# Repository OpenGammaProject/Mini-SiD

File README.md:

# Mini SiPM Driver (SiD) Board

**This is the latest hardware revision 4.x. For older revisions, please have a look at the [other branches](https://github.com/OpenGammaProject/Mini-SiD/branches). A comparison between the revision 3 and 4 hardware can be found [here on Hackaday](https://hackaday.io/project/188090-mini-sipm-driver-board/log/225429-revision-4-is-finally-here).**

**This project is on [Hackaday.io](https://hackaday.io/project/188090-mini-sipm-driver-board), where I also post project logs, progress updates and other announcements.**

Minimalistic board that allows you to quickly and easily utilize a silicon photomultiplier (SiPM) within your other projects. Supports a range of input voltages, has a digital (TTL) pulse output for the registered counts and a direct output for the SiPM pulses for easy expansion. Similar to the original [Open Gamma Detector](https://github.com/OpenGammaProject/Open-Gamma-Detector), but without any direct way to perform gamma spectroscopy.

All you need to build your own scintillation counter is this board, a scintillator and SiPM. The benefits of such a scintillation counter are that you can use it just like a Geiger counter, but it's much more sensitive, can be smaller, doesn't need 300+ Volts and you can also use it to do spectroscopy with some additional components. It mostly only registers gamma radiation though, so keep that in mind!

## How To Get One

* You can check out the project on PCBWay (affiliate) and if you buy through their service, it supports the project a little, and doesn’t cost you anything extra.
* Otherwise, use a PCB manufacturer and an electronics distributor of your choice and proceed on your own. All the files you'll need can be found in this repo.
* If you don't want to deal with all of that, feel free to contact me. Just send me an e-mail and I can help you out with the process.

**You will also need to buy a SiPM (e.g. the MICROFC-60035-SMT-TR) and scintillator (NaI(Tl) recommended) separately at a distributor of your choice.**

## Specifications

Here are some of the most important key facts:

* Compact design: Total size 100 x 25 mm. 50 x 25 mm area for electronics and additional 50 x 25 mm to mount a small scintillator.
* Input voltage: 3.1 V - 5.5 V.
* Low-voltage device: No HV needed like with a photomultiplier tube.
* SiPM voltage range from 27.5 V to 33.8 V.
* Low power consumption: <4 mA @ 5 V in standard operation.
* Adjustable gain for the SiPM pulses, also affects pulse decay time and therefore dead time.
* TTL output for counting pulses or time-over-threshold applications.
* Additional raw pulse output if you want to manipulate the signal or use it for spectroscopy.
* Dead time only limited by the speed of the scintillator and the gain. Typically only a few microseconds.
* Only needs an additional cheap microcontroller to, for example, build a simple scintillation counter.

## Working Principle

Here is a nice flow chart explaining how this device roughly works:

## Hardware

Hardware design has been done with [EasyEDA](https://easyeda.com/) and all the needed files for you to import the project as well as the schematic can be found in the `hardware` folder. There is also a Gerber file available for you to go directly to the PCB manufacturing step.

This project utilizes a silicon photomultiplier (short SiPM) which is way smaller and more robust than a traditional photomultiplier tube and does not need a high-voltage supply (traditionally  around 1000 V). Here are some very helpful in-depth datasheets about the particular MicroFC SiPM used here:

* [C-Series SiPM Sensors datasheet](https://www.onsemi.com/pdf/datasheet/microc-series-d.pdf)
* [Linearity of the Silicon Photomultiplier](https://www.onsemi.com/pub/Collateral/AND9776-D.PDF)
* [Introduction to the SiliconPhotomultiplier (SiPM)](https://www.onsemi.com/pub/Collateral/AND9770-D.PDF)
* [Biasing and Readout of ON Semiconductor SiPM Sensors](https://www.onsemi.com/pub/Collateral/AND9782-D.PDF)

PCB size is 10 x 2.5 cm. If you don't need the additional space to mechanically mount the SiPM/scintillator assembly to the rest of the detector board, you can just cut it off at the white line and you're left with a much smaller detector (~5.0 x 2.5 cm).

The PCB has four layers with components only at the top side. It mostly uses 0603 components or comparable IC packages to make it possible to solder it by hand and at the same time keep it as small as reasonable.
This combination makes for the best signal properties while still being fairly affordable with today's PCB manufacturing prices.

The TTL-compatible `INT` output is an active high pin!

**Here is a helpful image about the potentiometer settings (turning increases each setting):**

## 3D Model

If you want to design an enclosure for the PCB or you need a 3D model for whatever other reason, you can have a look at the files in the `3D` folder. It includes 3D models of the PCB itself and some of the components on the board.

## Scintillation Counter

A great project utilizing the Mini SiD is building a scintillation counter, which can be much more powerful than a geiger counter while being safer to use, because of the relatively low voltages.

One great example build has been done by [RD-Gamma](https://rd-gammaspectra.xyz), who built one such device using a russian scintillator and a Broadcom AFBR SiPM.

## Example Results

Here is a small collection of example results I got when measuring the count rate at the TTL output with my small 18 x 30 mm NaI(Tl) scintillator and a 6 mm MicroFC SiPM.

| Sample | Result Average [cps] |
| --- | --- |
| Background (no source) | 24 |
| Am-241 (commonly used in ionization smoke detectors) | 230 |
| Cup with Uraninite glaze (i.e. containing natural pitchblende) | 64 |
| 5g LYSO scintillator (containing naturally-occuring Lu-176) | 34 |
| Thorianite (mineral) | 800 |

## Some Ideas

### Coincidence Measurements

You can tie multiple boards' `INT` outputs together in an `AND` gate chip to only trigger a signal when all boards detected something. These AND gate ICs are very cheap, readily available and the output can then go into a microcontroller interrupt pin to count the gamma events.

To make the timing a bit easier for the gates and to consider delays, you can feed the board `INT` output into a [monostable multivibrator circuit](https://en.wikipedia.org/wiki/Multivibrator#Monostable) such as an NE555 timer IC. This will allow you to stretch all the signals by a certain time factor you can set.

---

Thanks for reading.

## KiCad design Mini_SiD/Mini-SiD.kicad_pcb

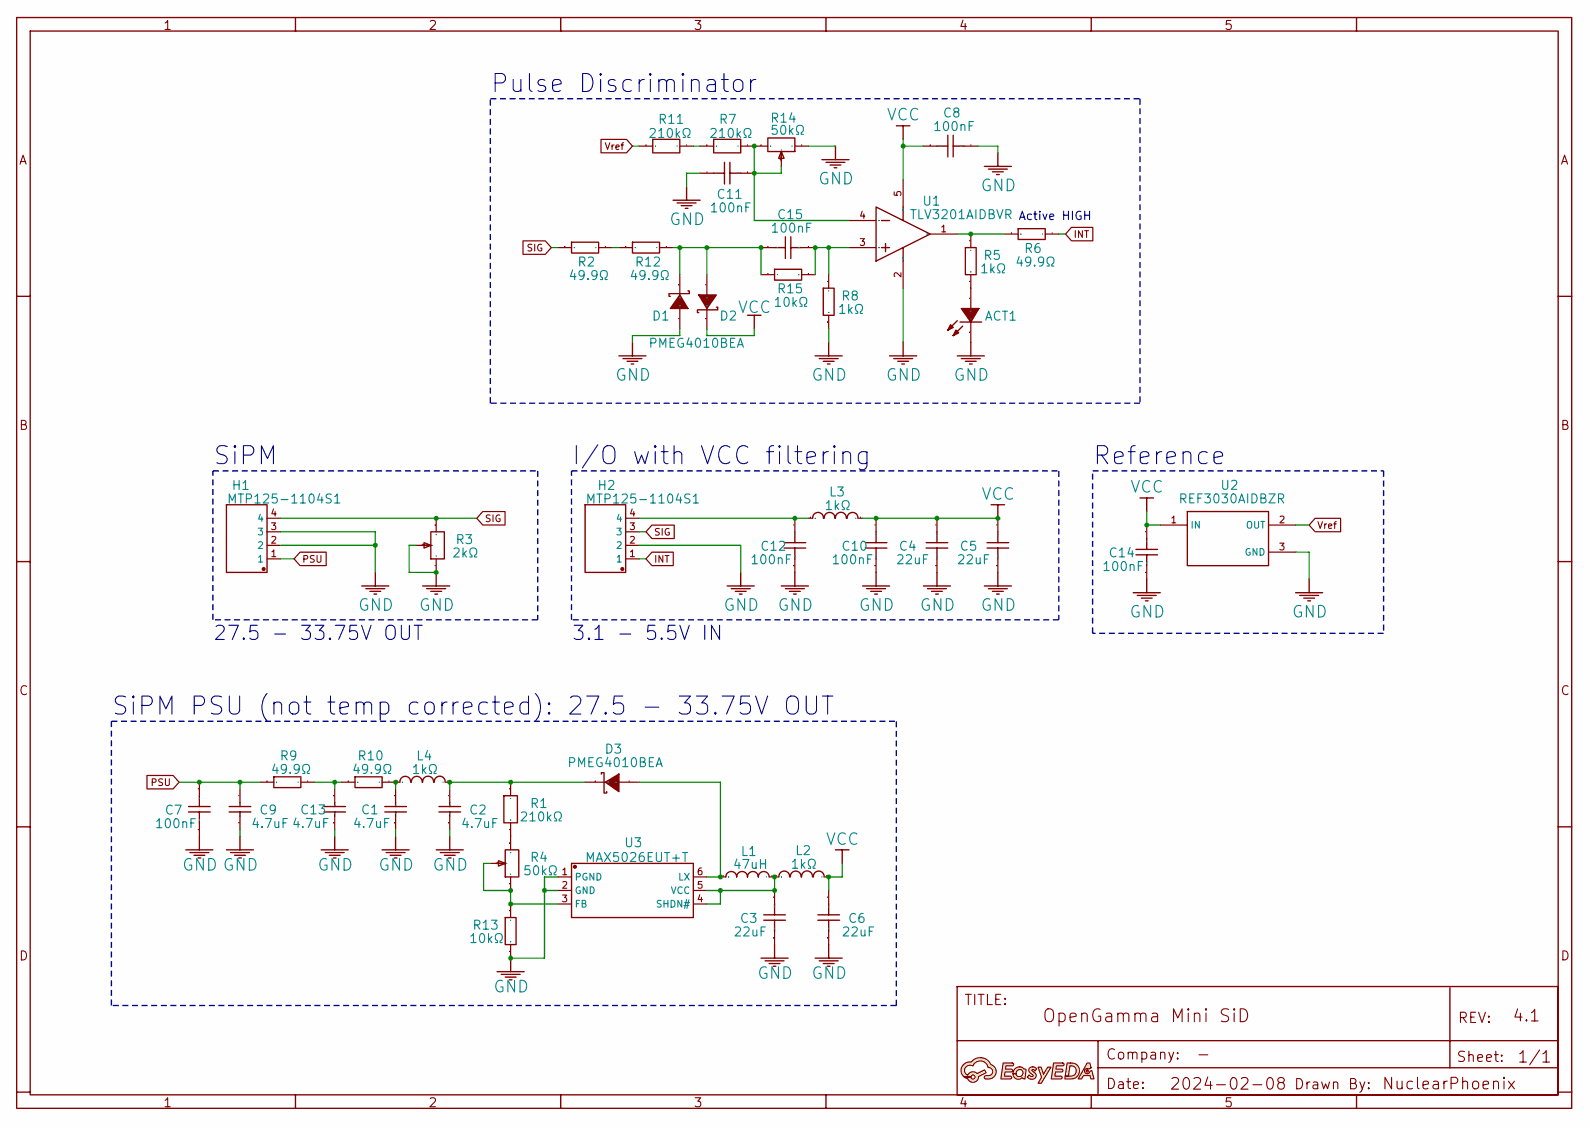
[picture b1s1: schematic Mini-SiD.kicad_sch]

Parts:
ACT1: LTST-C190KGKT; Manufacturer Part LTST-C190KGKT
C1, C2, C9, C13: 4.7uF; Manufacturer Part CL21A475KBQNNNE
C3, C4, C5, C6: 22uF; Manufacturer Part CL10A226MP8NUNE
C7, C8, C10, C11, C12, C14, C15: 100nF; Manufacturer Part CL10B104KC8NNNC
D1, D2, D3: PMEG4010BEA; Manufacturer Part PMEG4010BEA,115
H1, H2: MTP125-1104S1; Manufacturer Part MTP125-1104S1
L1: 47uH; Manufacturer Part NRS4018T470MDGJ
L2, L3, L4: 1kΩ; Manufacturer Part BLM18KG102SN1D
NO1: NO; Manufacturer Part ?
R1, R7, R11: 210kΩ; Manufacturer Part TC0325D2103T5H
R2, R6, R9, R10, R12: 49.9Ω; Manufacturer Part 0603WAF499JT5E
R3: 2kΩ; Manufacturer Part 3362P-1-202LF
R4, R14: 50kΩ; Manufacturer Part 3362P-1-503LF
R5, R8: 1kΩ; Manufacturer Part 0603WAJ0102T5E
R13, R15: 10kΩ; Manufacturer Part ARG03FTC1002
U1: TLV3201AIDBVR; Manufacturer Part TLV3201AIDBVR
U2: REF3030AIDBZR; Manufacturer Part REF3030AIDBZR
U3: MAX5026EUT+T; Manufacturer Part MAX5026EUT+T

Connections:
GND: ACT1.1 (-), C1.1, C2.1, C3.1, C4.1, C5.1, C6.1, C7.1, C8.2, C9.1, C10.1, C11.2, C12.1, C13.1, C14.1, D1.2 (A), H1.2, H1.3, H2.2, R3.2, R3.3, R8.1, R13.1, R14.3, U1.2 (GND), U2.3 (GND), U3.1 (PGND), U3.2 (GND); also elsewhere on the board
INT: H2.1, R6.2
unnamed: ACT1.2 (+), R5.1
unnamed: C1.2, L4.1, R10.2
unnamed: C12.2, H2.4, L3.1
unnamed: C13.2, R9.2, R10.1
unnamed: C15.2, D1.1 (K), D2.2 (A), R12.2, R15.2
unnamed: D3.2 (A), L1.1, U3.6 (LX)
unnamed: C2.2, D3.1 (K), L4.2, R1.2
unnamed: R1.1, R4.1
unnamed: R7.1, R11.2
unnamed: R2.2, R12.1
unnamed: C15.1, R8.2, R15.1, U1.3 (IN+)
unnamed: C11.1, R7.2, R14.1, R14.2, U1.4 (IN-)
unnamed: R5.2, R6.1, U1.1 (OUT)
unnamed: R4.2, R4.3, R13.2, U3.3 (FB)
unnamed: C3.2, L1.2, L2.1, U3.4 (SHDN#), U3.5 (VCC)
PSU: C7.2, C9.2, H1.1, R9.1
SIG: H1.4, H2.3, R2.1, R3.1
VCC: C4.2, C5.2, C6.2, C8.1, C10.2, C14.2, D2.1 (K), L2.2, L3.2, U1.5 (VCC), U2.1 (IN)
Vref: R11.1, U2.2 (OUT)

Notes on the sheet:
Active HIGH
Reference
I/O with VCC filtering
Pulse Discriminator
27.5 - 33.75V OUT
3.1 - 5.5V IN
SiPM
SiPM PSU (not temp corrected): 27.5 - 33.75V OUT

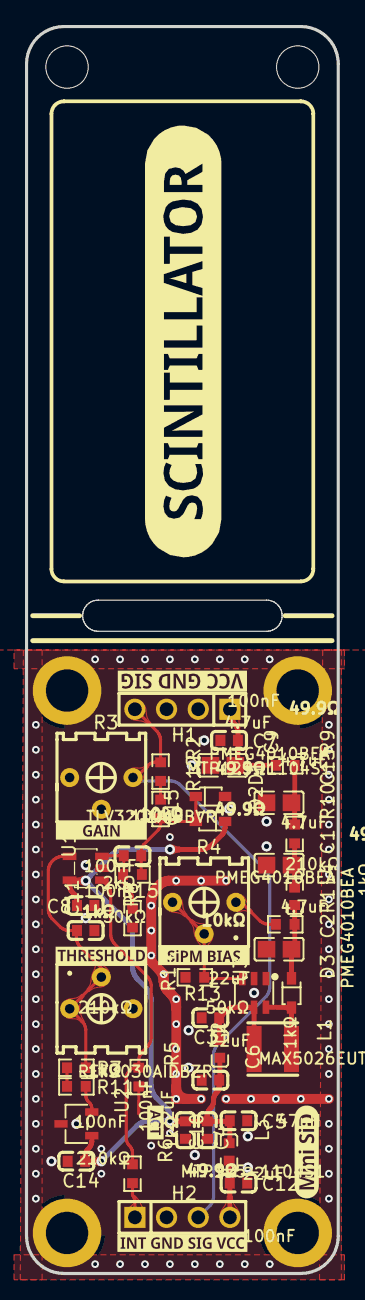
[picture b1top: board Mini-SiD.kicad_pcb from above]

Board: 4 copper layers, 25.0 x 100.0 mm, 48 parts (0 on the bottom side), 20 nets.

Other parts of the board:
Hole_gge8601: Hole_gge8601
Hole_gge14374: Hole_gge14374
Pad_gge4845: Pad_gge4845
Pad_gge5061: Pad_gge5061
Pad_gge8824: Pad_gge8824
Pad_gge8848: Pad_gge8848

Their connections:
GND: Pad_gge4845.1, Pad_gge5061.1, Pad_gge8824.1, Pad_gge8848.1; also elsewhere on the board

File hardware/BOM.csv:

You can find detailed documentation, photos, and example results there, along with links to project logs and community builds on Hackaday.io.;Name;Designator;Footprint;Quantity;Manufacturer Part;Manufacturer;Supplier;Supplier Part;Price
;10kΩ;R13,R15;R0603;2;0603WAF1002T5E;UNI-ROYAL(厚声);LCSC;C25804;0.001
Ordering your PCB through PCBWay helps support continued development of open-source radiation detection hardware.;1kΩ;R5,R8;R0603;2;0603WAF1001T5E;UNI-ROYAL(厚声);LCSC;C21190;0.001
3;2kΩ;R3;RES-ADJ-TH_3362P;1;3362P-1-202LF;BOURNS;LCSC;C111654;0.373
4;50kΩ;R4,R14;RES-ADJ-TH_3P-L7.1-W6.9-P2.50-L_3362P;2;3362P-1-503;BOCHEN(博晨);LCSC;C118910;0.143
5;100nF;C7,C8,C10,C11,C12,C14,C15;C0603;7;CL10B104KC8NNNC;SAMSUNG(三星);LCSC;C15725;0.006
6;TLV3201AIDBVR;U1;SOT-23-5_L3.0-W1.7-P0.95-LS2.8-BR;1;TLV3201AIDBVR;TI(德州仪器);LCSC;C105188;0.403
7;LTST-C190KGKT;ACT;LED0603-RD;1;LTST-C190KGKT;LITEON(光宝);LCSC;C125094;0.015
8;49.9Ω;R2,R6,R9,R10,R12;R0603;5;0603WAF499JT5E;UNI-ROYAL(厚声);LCSC;C23185;0.001
9;4.7uF;C1,C2,C9,C13;C0805;4;CL21A475KBQNNNE;SAMSUNG(三星);LCSC;C98192;0.02
10;REF3030AIDBZR;U2;SOT-23-3_L2.9-W1.6-P1.90-LS2.8-BR;1;REF3030AIDBZR;TI(德州仪器);LCSC;C38423;0.263
11;210kΩ;R1,R7,R11;R0603;3;TC0325D2103T5H;UNI-ROYAL(厚声);LCSC;C517422;0.023
12;22uF;C3,C4,C5,C6;C0603;4;CL10A226MP8NUNE;SAMSUNG(三星);LCSC;C86295;0.015
13;PMEG4010BEA;D1,D2,D3;SOD-323_L1.8-W1.3-LS2.5-RD;3;PMEG4010BEA,115;Nexperia(安世);LCSC;C36975;1.315
14;MTP125-1104S1;H1,H2;HDR-TH_4P-P2.54-V-M;2;MTP125-1104S1;MINTRON(明硕);LCSC;C358686;0.024
15;47uH;L1;IND-SMD_L4.0-W4.0_NR4018T;1;NRS4018T470MDGJ;TAIYO YUDEN(太诱);LCSC;C222886;0.126
16;1kΩ;L2,L3,L4;L0603;3;BLM18KG102SN1D;muRata(村田);LCSC;C160982;0.017
17;MAX5026EUT+T;U3;SOT-23-6_L2.9-W1.6-P0.95-LS2.8-BL;1;MAX5026EUT+T;ADI(亚德诺)/MAXIM(美信);LCSC;C87603;1.696

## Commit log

2022-11-02 add kitspace file
2022-11-02 Create LICENSE
2022-11-02 add docs files
2022-11-15 add hardware files
2022-11-15 [ImgBot] Optimize images
    *Total -- 101.44kb -> 52.99kb (47.76%)
    /docs/flow.drawio.png -- 26.55kb -> 9.24kb (65.22%)
    /docs/pcb_back.png -- 24.58kb -> 14.06kb (42.81%)
    /docs/pcb_front.png -- 50.30kb -> 29.70kb (40.97%)
2022-11-15 add docs
2022-11-15 bold arrow
2022-11-16 fix Kitspace Gerber preview
2022-11-18 add example sketch
2022-11-18 add hackaday link
2022-12-04 minor fixes
    i didn't change much at all, just some documentation corrections and lib updates
2023-01-11 Stop filtering out PCB services in kitspace.yaml
2023-01-16 Fix URLs
2023-01-16 Fix URL
2023-01-16 Fix more URLs
2023-02-24 add OSHWA certificate
2023-03-08 rev 3
2023-04-12 add gitignore
2023-04-12 very minor misc changes
2023-04-12 add photos
2023-04-12 fix line break
2023-04-12 add changelog post
2023-04-13 fix Tindie link
2023-04-13 [ImgBot] Optimize images
    *Total -- 1,540.28kb -> 1,415.24kb (8.12%)
    /docs/pcb_back.png -- 26.67kb -> 16.69kb (37.41%)
    /docs/pcb_front.png -- 38.81kb -> 25.29kb (34.84%)
    /docs/flow.drawio.svg -- 17.03kb -> 15.71kb (7.73%)
    /docs/img1.jpg -- 789.83kb -> 733.40kb (7.14%)
    /docs/img2.jpg -- 665.08kb -> 621.37kb (6.57%)
2023-04-13 add pot settings
2023-04-15 add example project
2023-04-15 [ImgBot] Optimize images
    *Total -- 93.08kb -> 78.99kb (15.14%)
    /docs/controls.png -- 38.94kb -> 24.86kb (36.17%)
    /docs/example.jpg -- 54.14kb -> 54.14kb (0.01%)
2023-04-19 Update OSHWA cert
2023-04-19 [ImgBot] Optimize images
    *Total -- 29.92kb -> 14.30kb (52.22%)
    /docs/pcb_back.png -- 27.08kb -> 11.52kb (57.44%)
    /docs/oshw.svg -- 2.85kb -> 2.78kb (2.54%)
2023-04-20 add 3D models
2023-05-17 Arduino UNO example
2023-07-27 Update example results
2023-09-08 Remove Tindie
2023-09-13 update oshwa svg
2023-09-19 decrease OSHW size
2023-11-22 format and update comments
2023-11-22 increase serial baud rate
2023-11-22 change color to red
2023-11-22 preliminary changes
2023-11-22 upload rev 4
2023-11-22 Update PCB layer note
2023-11-23 add hackaday comparison log
2023-11-29 add OSHWA cert
2023-11-30 [ImgBot] Optimize images
    *Total -- 134.45kb -> 88.11kb (34.47%)
    /docs/controls.png -- 43.34kb -> 26.37kb (39.16%)
    /docs/pcb_back.png -- 30.82kb -> 19.54kb (36.59%)
    /docs/pcb_front.png -- 46.77kb -> 29.67kb (36.55%)
    /docs/oshw.svg -- 13.54kb -> 12.54kb (7.39%)
2024-03-01 add rev 4.1
2024-03-01 remove ad
2024-06-04 add email support note
2024-11-14 fix missing R15 from PCB
    Also pulled EasyEDA library updates for all components at the same time
    No functional changes
2025-02-22 add pick and place file
2025-02-22 add project file
2025-06-18 fix svg text
2025-06-18 [ImgBot] Optimize images
    *Total -- 247.05kb -> 210.13kb (14.95%)
    /docs/pcb_back.png -- 39.27kb -> 26.62kb (32.22%)
    /docs/pcb_front.png -- 68.54kb -> 46.86kb (31.64%)
    /docs/flow.drawio.svg -- 139.24kb -> 136.66kb (1.86%)
2025-11-13 fix project files
2025-11-13 add PCBWay affiliate
2025-12-26 remove kitspace
2026-01-29 Add Mini_SiD project files (hardware, examples, docs)
2026-06-17 update tld
